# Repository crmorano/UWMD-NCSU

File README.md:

UWMD-NCSU
=========

Underwater Metal Detector Design

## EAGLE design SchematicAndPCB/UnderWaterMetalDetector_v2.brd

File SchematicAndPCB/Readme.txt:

Group 6, UnderWater Metal Detector
Chris Morano
Dorian Perry
Bryson Pender

UnderWaterMetalDetector_v2.brd - EAGLE Board File
UnderWaterMetalDetector_v2.sch - EAGLE Schematic File
UnderWaterMetalDetector_v2.pdf - PDF of Eagle Schematic File
UWMD-BuildBOM.xlsx - Build BOM
UWMD-SeniorDesign-SeeedGerbers.zip - Gerber Files for SeeedStudio's Fusion PCB Service

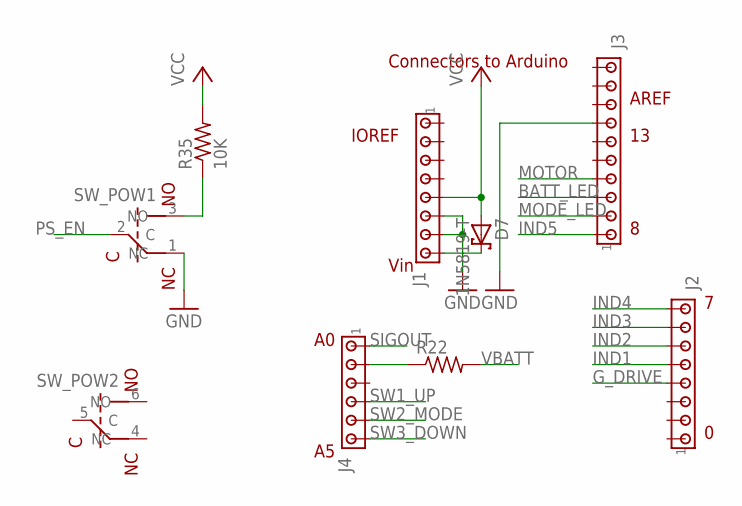
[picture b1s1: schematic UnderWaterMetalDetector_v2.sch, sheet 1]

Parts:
D7: 1N5819-T; DO41-7.6
J1, J2: MTA08-100; 10X08MTA
J3: MTA10-100; 10X10MTA
J4: MTA06-100; 10X06MTA
R22: R-US_R1206; R1206
R35: 10K; R1206
SW_POW: SW-TL2201EEYA

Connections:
BATT_LED: J3.3; also elsewhere on the board
GND: J1.6, J1.7, J3.7, SW_POW.1 (NC); also elsewhere on the board
G_DRIVE: J2.4; also elsewhere on the board
IND1: J2.5; also elsewhere on the board
IND2: J2.6; also elsewhere on the board
IND3: J2.7; also elsewhere on the board
IND4: J2.8; also elsewhere on the board
IND5: J3.1; also elsewhere on the board
MODE_LED: J3.2; also elsewhere on the board
MOTOR: J3.4; also elsewhere on the board
unnamed: J4.5 (2), R22.1
unnamed: D7.C, J1.8
unnamed: R35.1, SW_POW.3 (NO)
PS_EN: SW_POW.2 (C); also elsewhere on the board
SIGOUT: J4.6 (1); also elsewhere on the board
SW1_UP: J4.3 (4); also elsewhere on the board
SW2_MODE: J4.2 (5); also elsewhere on the board
SW3_DOWN: J4.1 (6); also elsewhere on the board
VBATT: R22.2; also elsewhere on the board
VCC: D7.A, J1.5, R35.2; also elsewhere on the board

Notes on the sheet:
Vin
IOREF
AREF
Connectors to Arduino

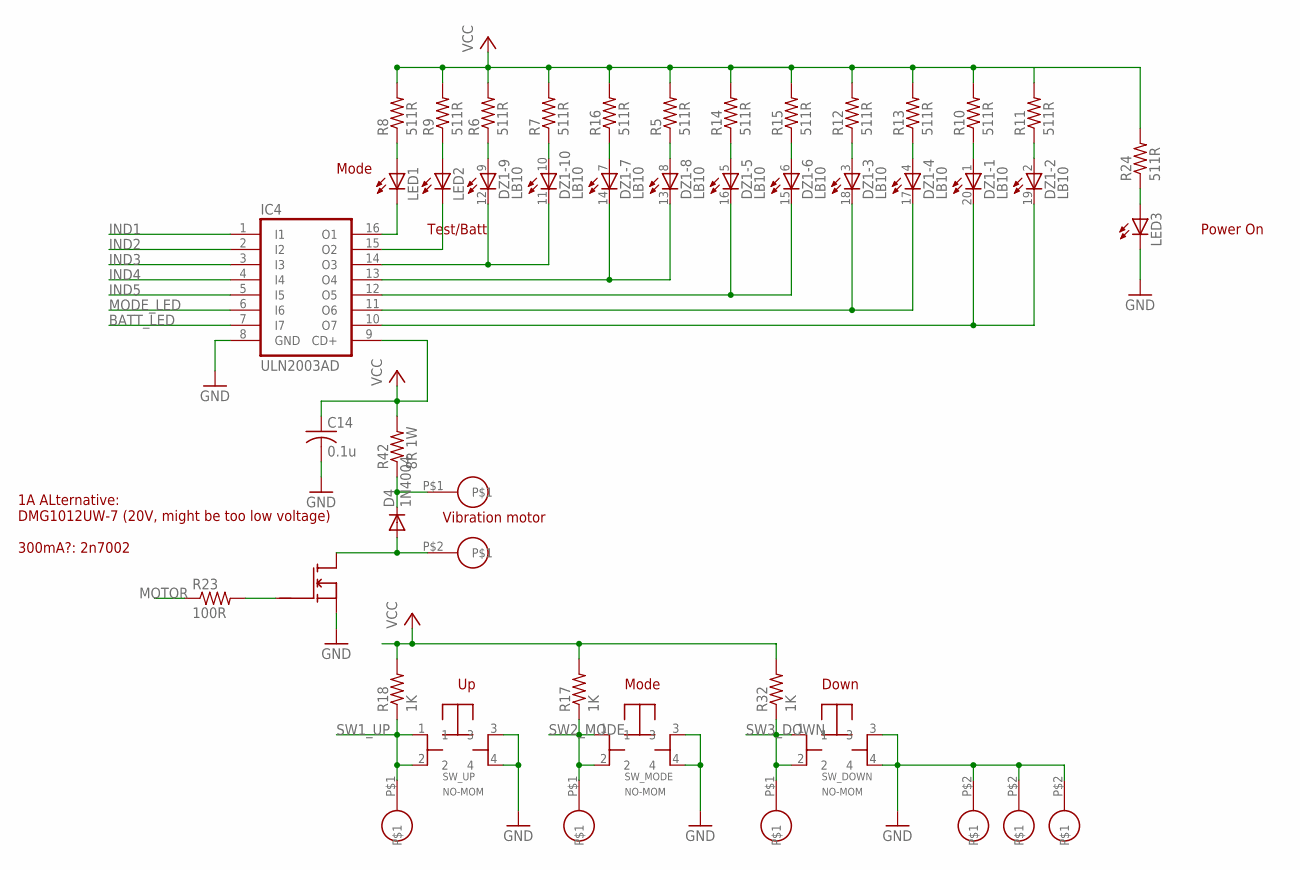
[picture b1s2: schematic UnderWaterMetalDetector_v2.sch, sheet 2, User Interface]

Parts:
C14: 0.1u; C1206
D4: 1N4004; DO41-10
DOWN: CON-SIP2-0.1
DZ1: LB10
IC4: ULN2003AD; SO16
LED1, LED2, LED3: LED5MM
MODE: CON-SIP2-0.1
MOTOR: CON-SIP2-0.1
Q2: FET-2N7000; TO92
R5, R6, R7, R8, R9, R10, R11, R12, R13, R14, R15, R16, R24: 511R; M1206
R17, R18, R32: 1K; M1206
R23: 100R; R1206
R42: 8R 1W; R2512
SW_DOWN: SW-SCHURTER-1301.9306
SW_MODE: SW-SCHURTER-1301.9306
SW_UP: SW-SCHURTER-1301.9306
UP: CON-SIP2-0.1

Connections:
BATT_LED: IC4.7 (I7); also elsewhere on the board
GND: C14.2, DOWN.P$2, IC4.8 (GND), LED3.K (C), MODE.P$2, Q2.1 (S), SW_DOWN.3, SW_DOWN.4, SW_MODE.3, SW_MODE.4, SW_UP.3, SW_UP.4, UP.P$2; also elsewhere on the board
IND1: IC4.1 (I1); also elsewhere on the board
IND2: IC4.2 (I2); also elsewhere on the board
IND3: IC4.3 (I3); also elsewhere on the board
IND4: IC4.4 (I4); also elsewhere on the board
IND5: IC4.5 (I5); also elsewhere on the board
MODE_LED: IC4.6 (I6); also elsewhere on the board
MOTOR: R23.1; also elsewhere on the board
unnamed: D4.C, MOTOR.P$1, R42.1
unnamed: DZ1.17 (C), DZ1.18 (C), IC4.11 (O6)
unnamed: Q2.2 (G), R23.2
unnamed: LED3.A, R24.1
unnamed: DZ1.19 (C), DZ1.20 (C), IC4.10 (O7)
unnamed: DZ1.15 (C), DZ1.16 (C), IC4.12 (O5)
unnamed: DZ1.13 (C), DZ1.14 (C), IC4.13 (O4)
unnamed: DZ1.11 (C), DZ1.12 (C), IC4.14 (O3)
unnamed: IC4.16 (O1), LED1.K (C)
unnamed: IC4.15 (O2), LED2.K (C)
unnamed: LED2.A, R9.1
unnamed: LED1.A, R8.1
unnamed: DZ1.10 (A), R7.1
unnamed: DZ1.9 (A), R6.1
unnamed: DZ1.8 (A), R5.1
unnamed: DZ1.1 (A), R10.1
unnamed: DZ1.2 (A), R11.1
unnamed: DZ1.3 (A), R12.1
unnamed: DZ1.4 (A), R13.1
unnamed: DZ1.5 (A), R14.1
unnamed: DZ1.6 (A), R15.1
unnamed: DZ1.7 (A), R16.1
unnamed: D4.A, MOTOR.P$2, Q2.3 (D)
SW1_UP: R18.1, SW_UP.1, SW_UP.2, UP.P$1; also elsewhere on the board
SW2_MODE: MODE.P$1, R17.1, SW_MODE.1, SW_MODE.2; also elsewhere on the board
SW3_DOWN: DOWN.P$1, R32.1, SW_DOWN.1, SW_DOWN.2; also elsewhere on the board
VCC: C14.1, IC4.9 (CD+), R5.2, R6.2, R7.2, R8.2, R9.2, R10.2, R11.2, R12.2, R13.2, R14.2, R15.2, R16.2, R17.2, R18.2, R24.2, R32.2, R42.2; also elsewhere on the board

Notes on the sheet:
Vibration motor
Mode
Test/Batt
Down
1A ALternative: DMG1012UW-7 (20V, might be too low voltage) 300mA?: 2n7002
Power On

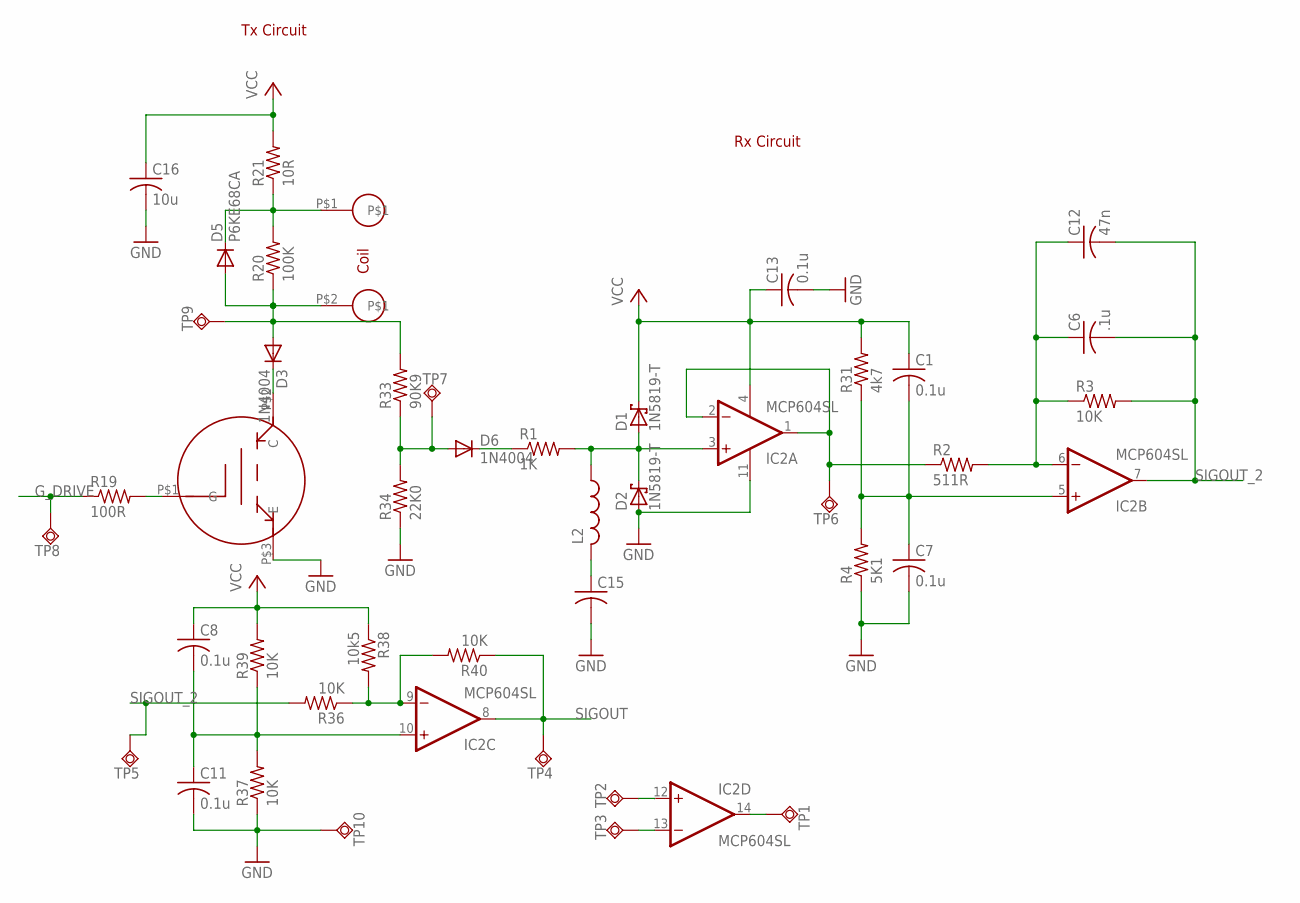
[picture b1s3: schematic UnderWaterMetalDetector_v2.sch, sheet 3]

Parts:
C1, C7, C8, C11, C13: 0.1u; C1206
C6: .1u; C1206
C12: 47n; C1206
C15: C-USC1206; C1206
C16: 10u; C1206
COIL: CON-SIP2-0.1
D1, D2: 1N5819-T; DO41-7.6
D3, D6: 1N4004; DO41-10
D5: P6KE68CA; D-5
IC2: MCP604SL; SO14
L2: L-US0204V; 0204V
Q1: STGP18N40LZ; TO-220-HORIZ
R1: 1K; M1206
R2: 511R; R1206
R3: 10K; R1206
R4: 5K1; R1206
R19: 100R; R1206
R20: 100K; M1206
R21: 10R; R2512
R31: 4k7; R1206
R33: 90K9; M1206
R34: 22K0; M1206
R36, R37, R39, R40: 10K; M1206
R38: 10k5; M1206
TP1, TP2, TP3, TP4, TP5, TP6, TP7, TP8, TP9, TP10: TPSQPAD1-13; P1-13

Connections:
GND: C7.2, C11.2, C13.2, C15.2, C16.2, D2.A, IC2.11 (V-), Q1.P$3 (E), R4.1, R34.1, R37.1, TP10.TP; also elsewhere on the board
G_DRIVE: R19.1, TP8.TP; also elsewhere on the board
unnamed: IC2.1 (OUT), IC2.2 (-IN), R2.1, TP6.TP
unnamed: D1.A, D2.C, IC2.3 (+IN), L2.1, R1.2
unnamed: D6.C, R1.1
unnamed: C1.2, C7.1, IC2.5 (+IN), R4.2, R31.1
unnamed: C8.2, C11.1, IC2.10 (+IN), R37.2, R39.1
unnamed: D6.A, R33.1, R34.2, TP7.TP
unnamed: C6.1, C12.1, IC2.6 (-IN), R2.2, R3.1
unnamed: IC2.9 (-IN), R36.1, R38.2, R40.2
unnamed: IC2.12 (+IN), TP2.TP
unnamed: IC2.13 (-IN), TP3.TP
unnamed: IC2.14 (OUT), TP1.TP
unnamed: C15.1, L2.2
unnamed: COIL.P$1, D5.C, R20.2, R21.1
unnamed: D3.C, Q1.P$2 (C)
unnamed: Q1.P$1 (G), R19.2
RXIN: COIL.P$2, D3.A, D5.A, R20.1, R33.2, TP9.TP
SIGOUT: IC2.8 (OUT), R40.1, TP4.TP; also elsewhere on the board
SIGOUT_2: C6.2, C12.2, IC2.7 (OUT), R3.2, R36.2, TP5.TP
VCC: C1.1, C8.1, C13.1, C16.1, D1.C, IC2.4 (V+), R21.2, R31.2, R38.1, R39.2; also elsewhere on the board

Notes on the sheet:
Coil
Tx Circuit
Rx Circuit

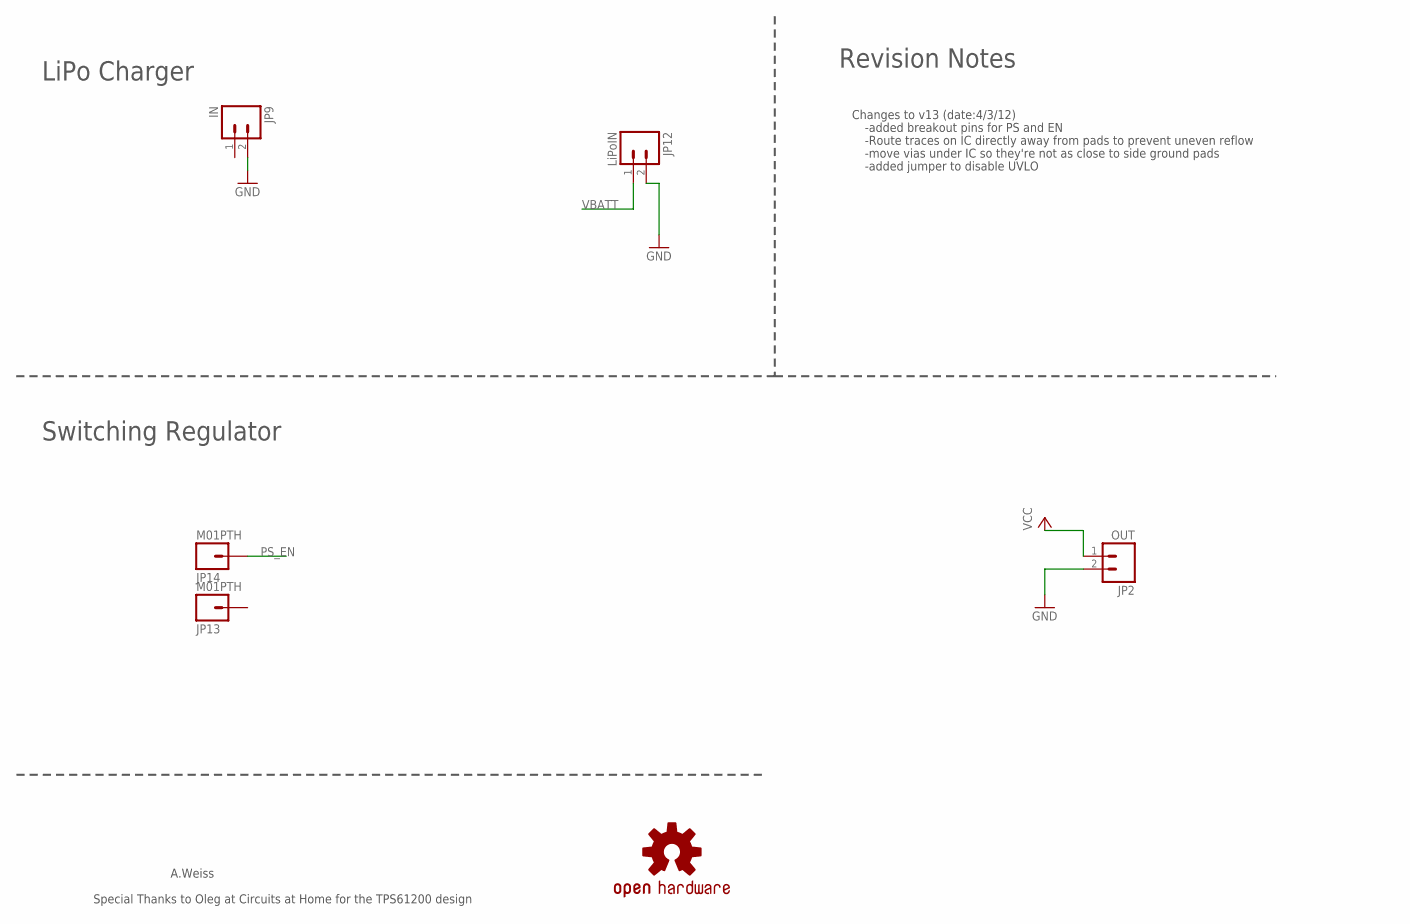
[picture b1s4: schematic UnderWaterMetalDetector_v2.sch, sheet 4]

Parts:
JP2: OUT; 1X02
JP9: IN; 1X02
JP12: LiPoIN; 1X02
JP13, JP14: M01PTH; 1X01
U$3: OSHW-LOGOS; OSHW-LOGO-S

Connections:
GND: JP2.2, JP9.2, JP12.2; also elsewhere on the board
PS_EN: JP14.1; also elsewhere on the board
VBATT: JP12.1; also elsewhere on the board
VCC: JP2.1; also elsewhere on the board

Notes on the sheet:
Changes to v13 (date:4/3/12)
-added breakout pins for PS and EN
-Route traces on IC directly away from pads to prevent uneven reflow
-move vias under IC so they're not as close to side ground pads
-added jumper to disable UVLO
A.Weiss
Special Thanks to Oleg at Circuits at Home for the TPS61200 design
LiPo Charger
Switching Regulator
Revision Notes

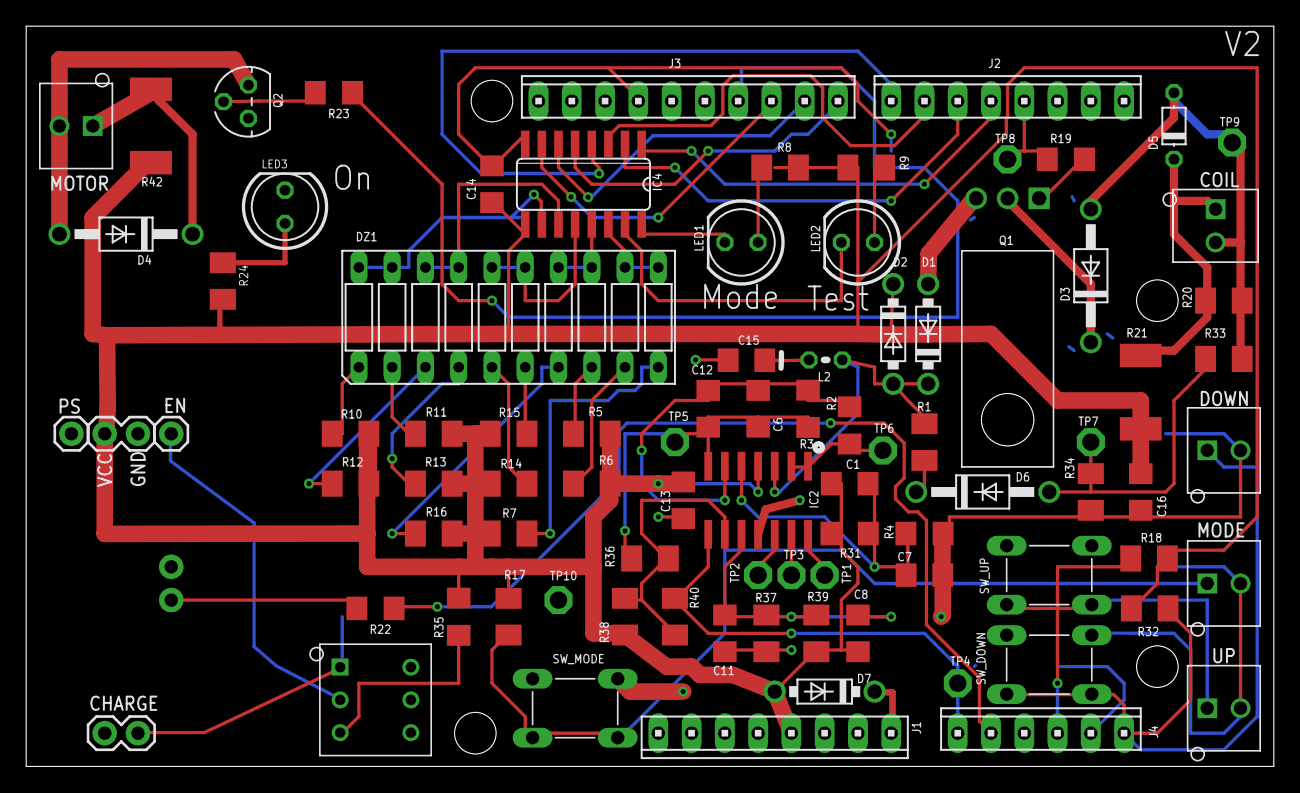
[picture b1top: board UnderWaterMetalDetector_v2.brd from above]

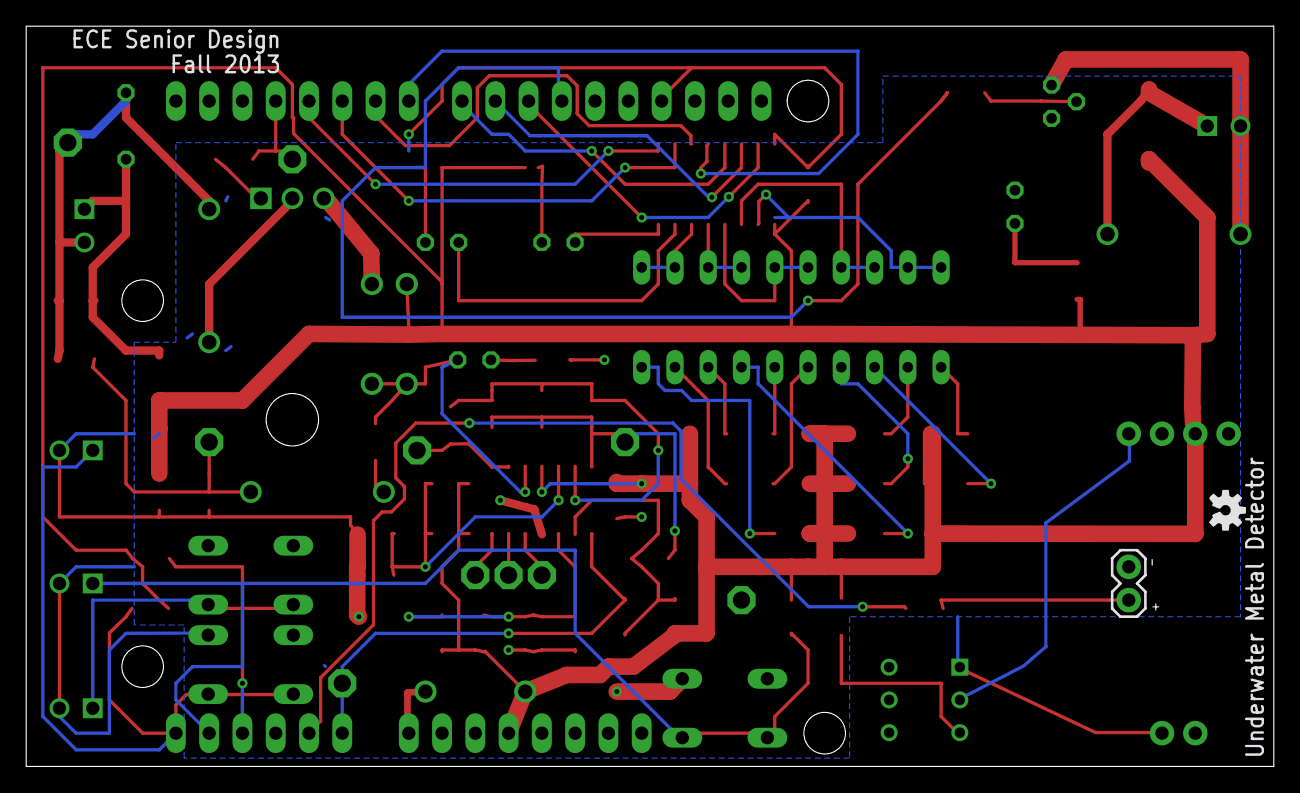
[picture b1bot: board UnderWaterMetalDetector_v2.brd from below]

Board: 2 copper layers, 95.2 x 56.5 mm, 90 parts (2 on the bottom side), 60 nets.

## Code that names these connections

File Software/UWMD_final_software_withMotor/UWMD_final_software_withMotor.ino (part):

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int numberOfLEDs = 5; //number of led groups in signal array
int led[5]; //Size = numberOfLEDs

int g_drive = 3; //coil output
int g_input = A0; //coil input

int mode_led = 4;//mode output
int mode_sw = A4;//mode input
int mode_state = 0;
int mode_led_state = 0;
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int down_sw = A5;//down button in
char down_button_hit = 0;

int batt_led = 5;// battery display
int batt_led_state = 0;
//int battLevel = 1;
int calValue = 950; //no metal
int outputValue = 0;

int motor_port = 11;
boolean buttons_run_once = false;


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//------------------------------------------SET UP-------------------------------------------------------------------------------
void setup() 
{ 
  pinMode(motor_port, OUTPUT);            //motor state
  digitalWrite(motor_port, LOW);

  pinMode(mode_led, OUTPUT);            //configure additional state LEDs for Mode transitions &
  digitalWrite(mode_led, LOW);
  pinMode(batt_led, OUTPUT);            //battery state
  digitalWrite(batt_led, LOW);
  

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
  
  pinMode(g_input,INPUT);               //setup coil reading pin
  pinMode(g_drive,OUTPUT);              //setup driving interface for coil
  digitalWrite(g_drive, LOW);           //intialize as low
  analogReference(INTERNAL);            //reference voltage between 1.0v - 1.2v

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
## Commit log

2013-11-25 Adding Code Files for Arduino Uno R3
    UWMD_final_software.ino most recent, includes a test file
    SeniorDesign_Software.ino
2013-12-06 Updated for Final Design
    Added the PCB, Added Schematic, Added BOM, Code now works properly and
    with the motor.
2013-12-06 Updates
    Added Readme, updated Build BOM to include Wire, Added SeeedStudio
    Gerbers.
